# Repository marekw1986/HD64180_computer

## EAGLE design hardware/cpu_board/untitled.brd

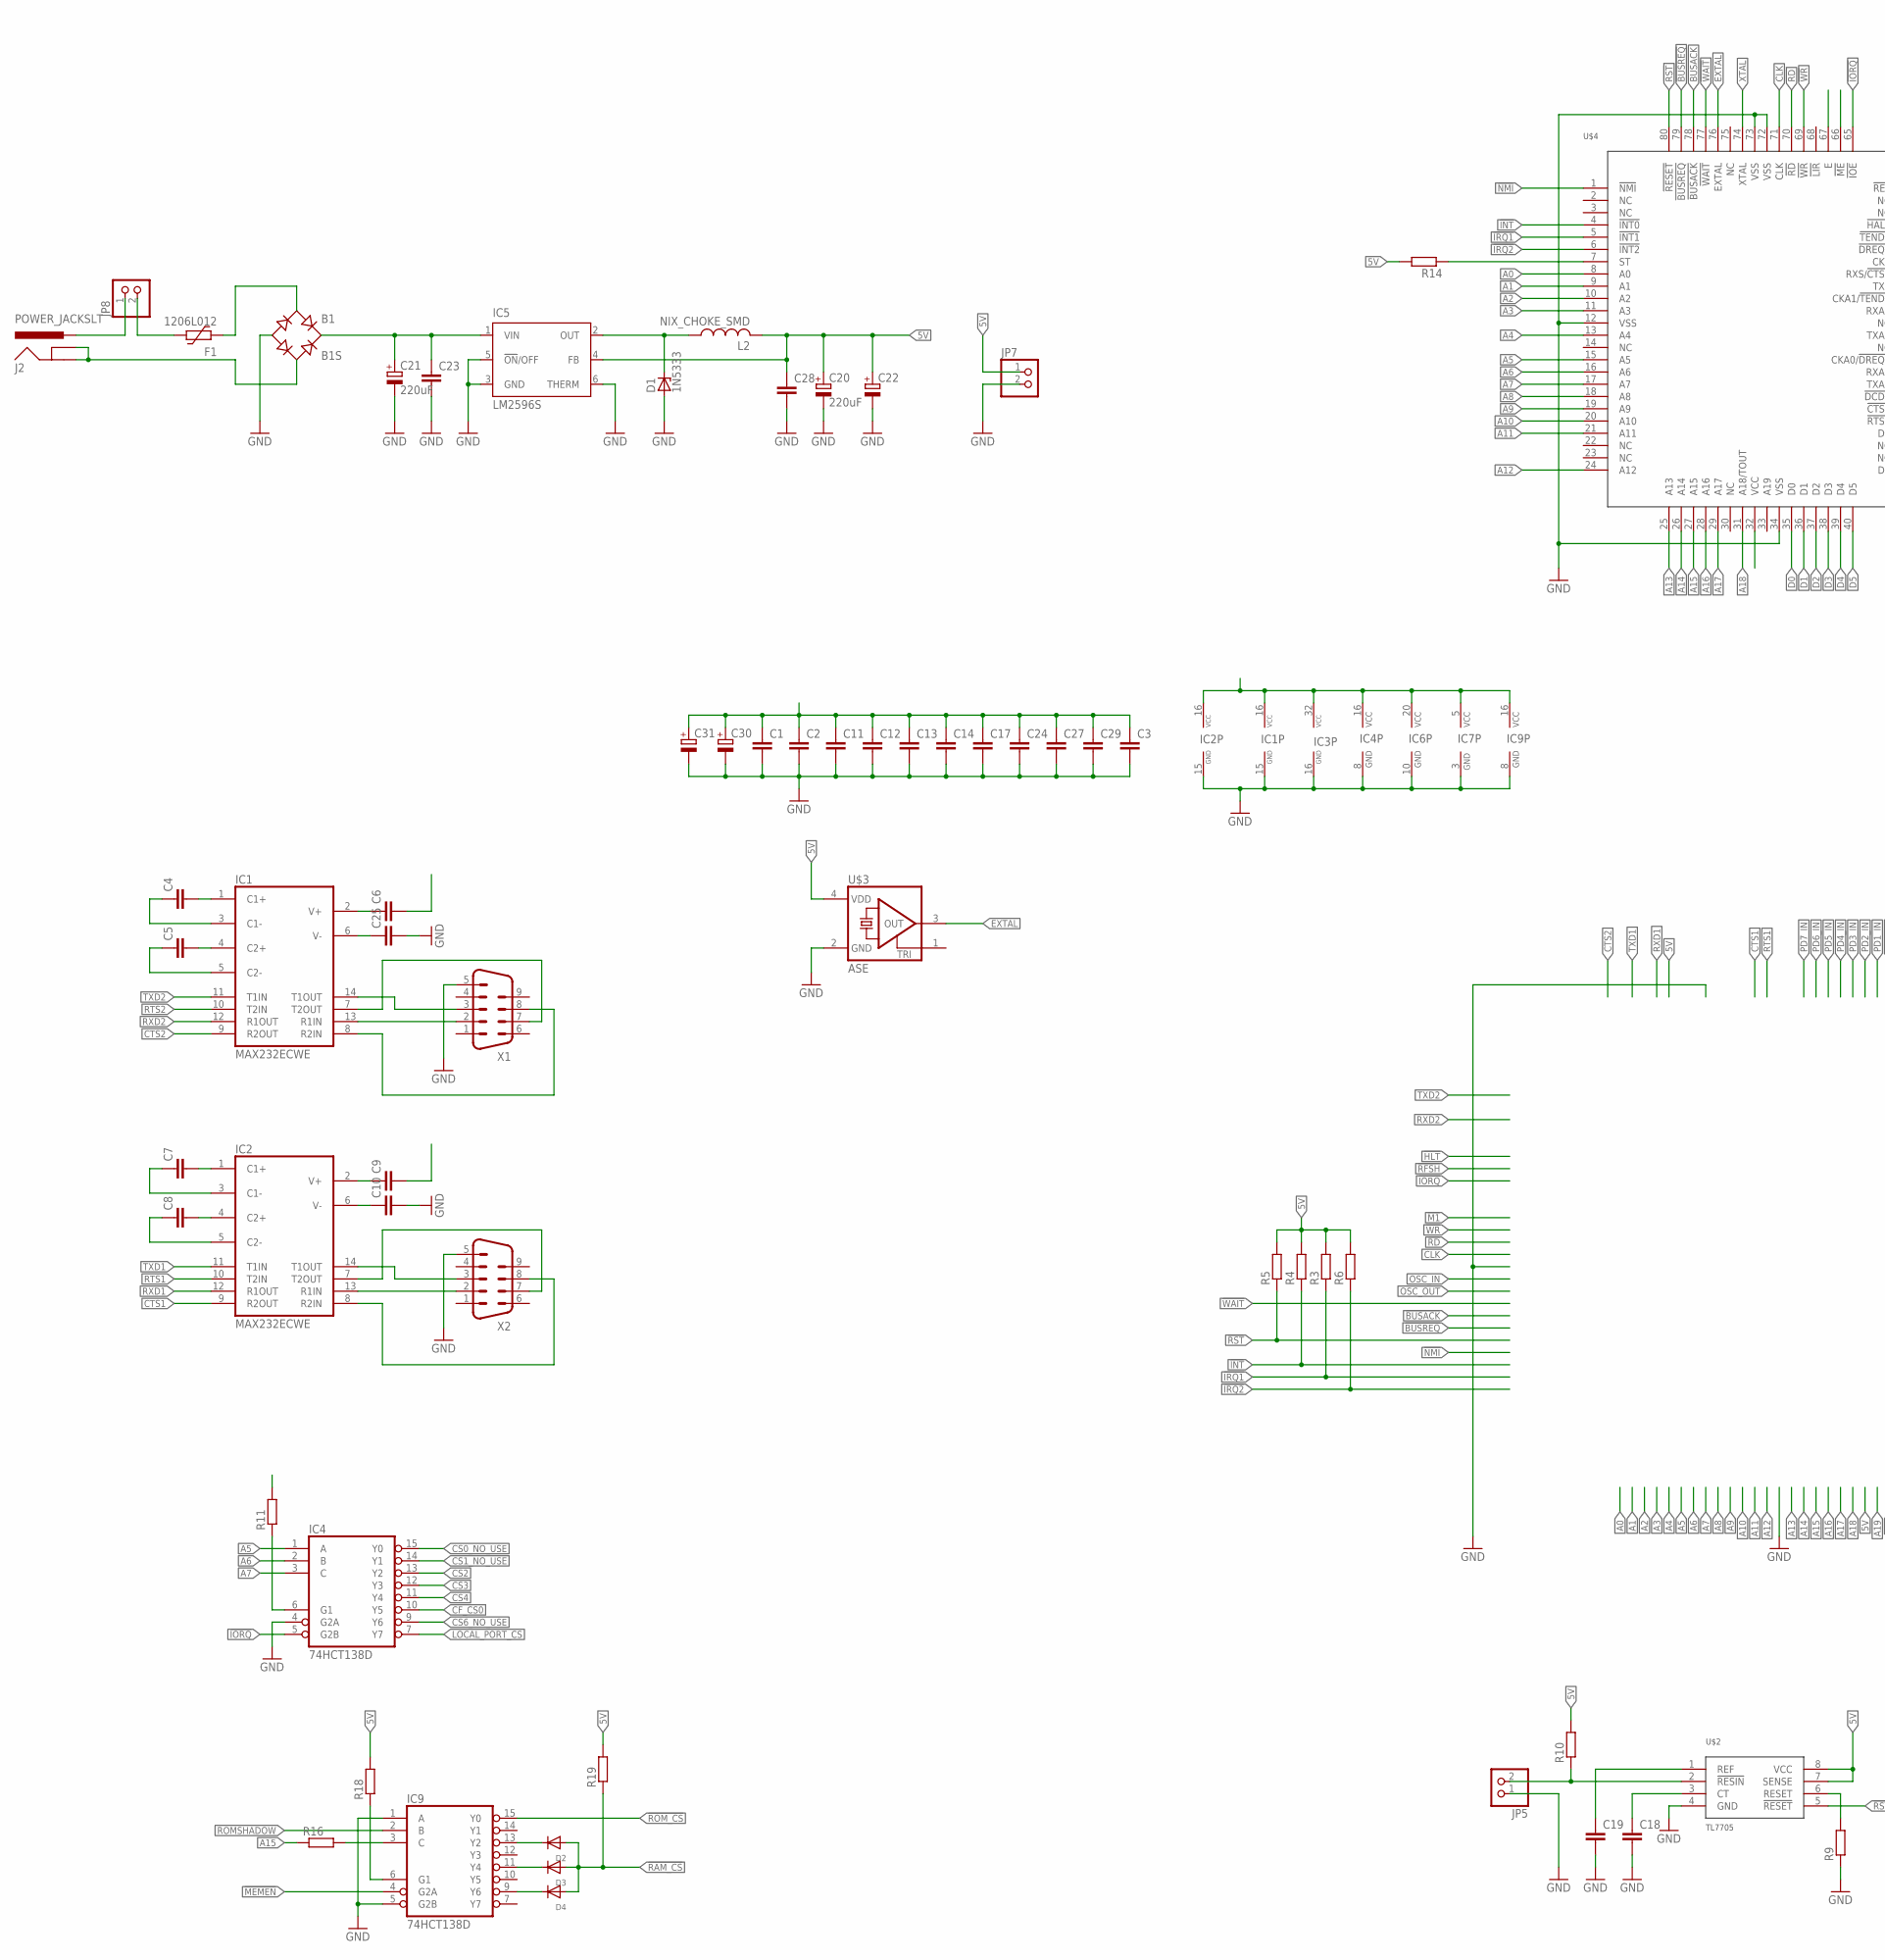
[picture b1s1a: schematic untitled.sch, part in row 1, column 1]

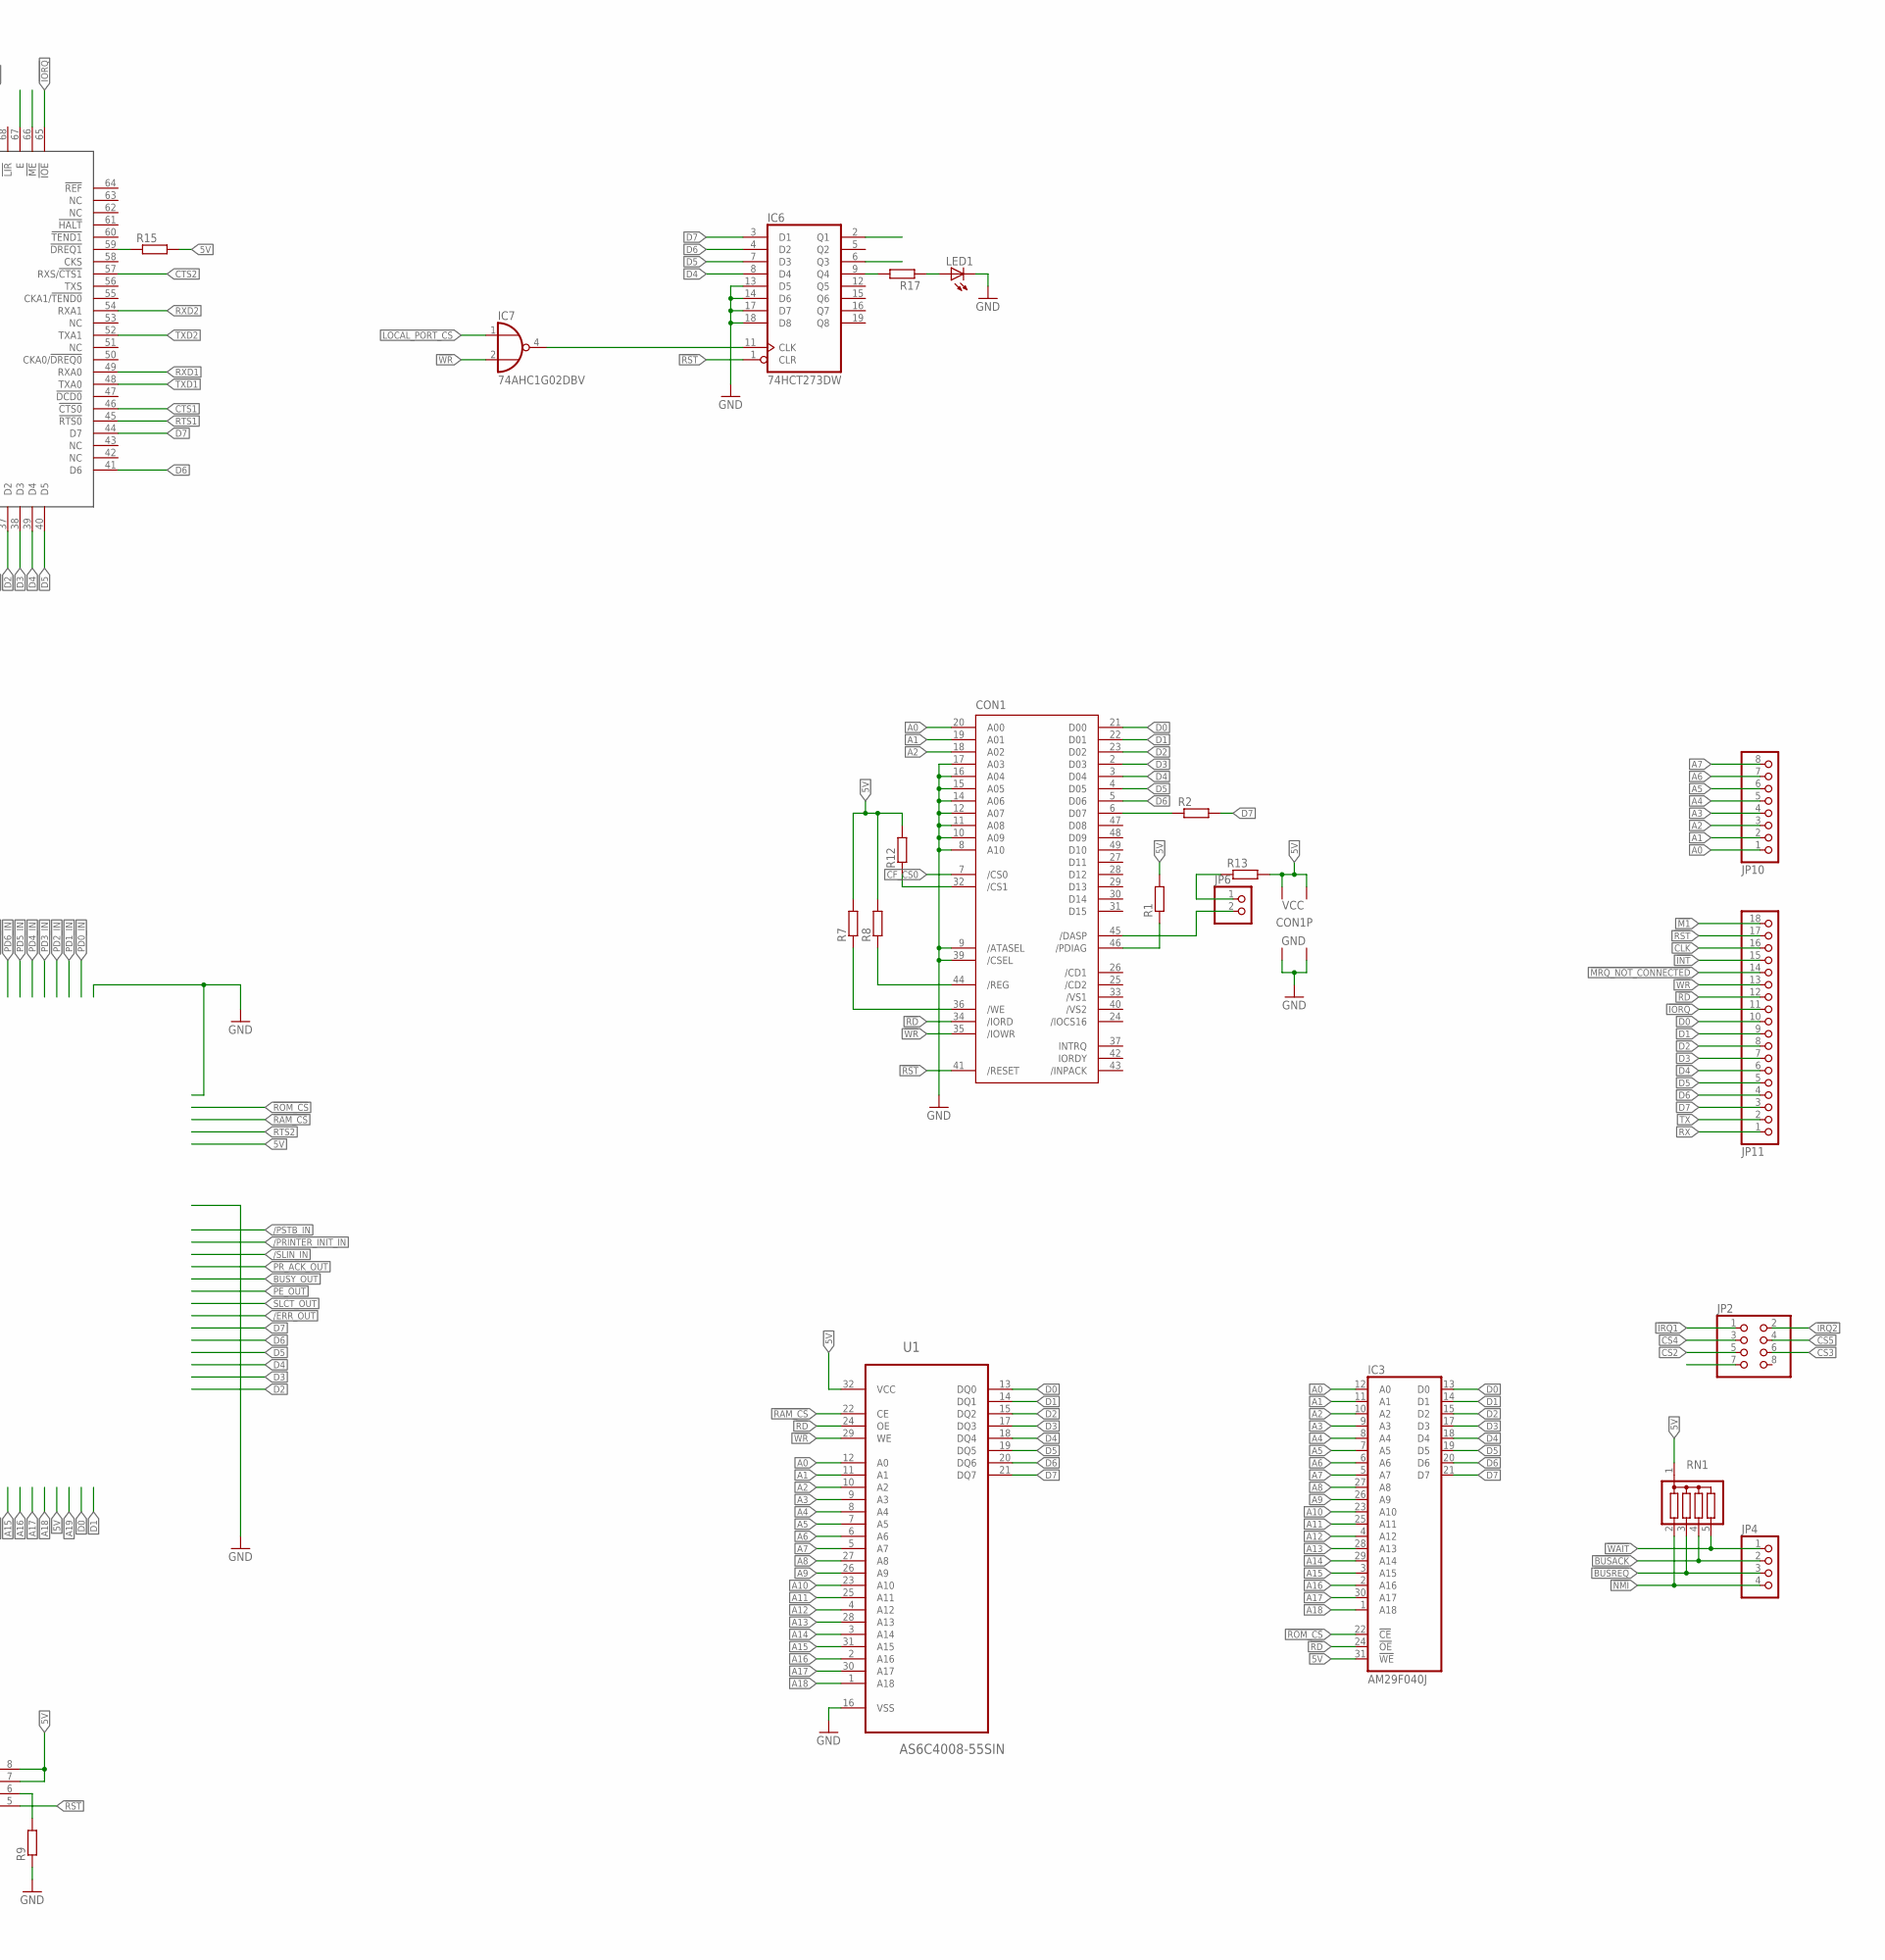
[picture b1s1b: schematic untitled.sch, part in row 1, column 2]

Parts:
B1: B1S; MBS
C1, C2, C3, C4, C5, C6, C7, C8, C9, C10, C11, C12, C14, C17, C18, C19, C23, C24, C25, C27, C28, C29: C-EUC0603; C0603
C13: C-EUC0402; C0402
C20, C21: 220uF; 153CLV-0810
C22: CPOL-EUSMCC; SMC_C
C30, C31: CPOL-EUSMCB; SMC_B
CON1: CF-CARD-IDE_MODE; MI20-50PD-SF
D1: 1N5333; C1702-15
D2, D3, D4: DIODESOD-323; SOD-323
F1: 1206L012; 1206L
IC1, IC2: MAX232ECWE; SO16L
IC3: AM29F040J; PLCC32R
IC4, IC9: 74HCT138D; SO16
IC5: LM2596S; TO263-5
IC6: 74HCT273DW; SO20W
IC7: 74AHC1G02DBV; SOT23-5
J2: POWER_JACKSLT; POWER_JACK_SLOT
JP2: PINHD-2X4; 2X04
JP4: PINHD-1X4; 1X04
JP5, JP6, JP7, JP8: PINHD-1X2; 1X02
JP10: PINHD-1X8; 1X08
JP11: PINHD-1X18; 1X18
L2: NIX_CHOKE_SMD
LED1: LEDCHIP-LED0603; CHIP-LED0603
R1, R2, R7, R8, R9, R11, R12, R13, R15, R16, R17, R18, R19: R-EU_R0603; R0603
R3, R4, R6: R-EU_R0402; R0402
R5: R-EU_R1206; R1206
R10: R-EU_M1206; M1206
R14: R-EU_0204/5; 0204/5
RN1: G04R; SIL5
U1: AS6C4008-55SIN; SOIC127P1407X299-32N
U$2: TL7705; SOIC8
U$3: ASE
U$4: HD64180QFP80_; QFP80
X1, X2: M09HP

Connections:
5V: C1.1, C2.1, C3.1, C6.2, C9.2, C11.1, C12.1, C13.1, C14.1, C17.1, C20.+, C22.+, C24.1, C27.1, C28.1, C29.1, C30.+, C31.+, CON1.13 (VCC2), CON1.38 (VCC1), IC1.16 (VCC), IC2.16 (VCC), IC3.31 (!WE), IC3.32 (VCC), IC4.16 (VCC), IC5.4 (FB), IC6.20 (VCC), IC7.5 (VCC), IC9.16 (VCC), JP7.1, L2.P$2 (2), R1.2, R3.2, R4.2, R5.2, R6.2, R7.2, R8.2, R10.2, R11.2, R12.2, R13.2, R14.2, R15.2, R18.2, R19.2, RN1.1, U1.32 (VCC), U$2.7 (SENSE), U$2.8 (VCC), U$3.4 (VDD), U$4.32 (VCC)
!BUSACK: JP4.2, RN1.4, U$4.78 (!BUSACK)
!BUSREQ: JP4.3, RN1.3, U$4.79 (!BUSREQ)
!INT: JP11.15, R4.1, U$4.4 (!INT0)
!IORQ: IC4.5 (G2B), JP11.11, U$4.65 (!IOE)
!IRQ1: JP2.1, R3.1, U$4.5 (!INT1)
!IRQ2: JP2.2, R6.1, U$4.6 (!INT2)
!M1: JP11.18
!MEMEN: IC9.4 (G2A), U$4.66 (!ME)
!MRQ_NOT_CONNECTED: JP11.14
!NMI: JP4.4, RN1.2, U$4.1 (!NMI)
!RAM_CS: D2.A, D3.A, D4.A, R19.1, U1.22 (CE)
!RD: CON1.34 (/IORD), IC3.24 (!OE), JP11.12, U1.24 (OE), U$4.70 (!RD)
!ROM_CS: IC3.22 (!CE), IC9.15 (Y0)
!RST: CON1.41 (/RESET), IC6.1 (CLR), JP11.17, R5.1, U$2.5 (!RESET), U$4.80 (!RESET)
!WAIT: JP4.1, RN1.5, U$4.77 (!WAIT)
!WR: CON1.35 (/IOWR), IC7.2 (I1), JP11.13, U1.29 (WE), U$4.69 (!WR)
A0: CON1.20 (A00), IC3.12 (A0), JP10.1, U1.12 (A0), U$4.8 (A0)
A1: CON1.19 (A01), IC3.11 (A1), JP10.2, U1.11 (A1), U$4.9 (A1)
A2: CON1.18 (A02), IC3.10 (A2), JP10.3, U1.10 (A2), U$4.10 (A2)
A3: IC3.9 (A3), JP10.4, U1.9 (A3), U$4.11 (A3)
A4: IC3.8 (A4), JP10.5, U1.8 (A4), U$4.13 (A4)
A5: IC3.7 (A5), IC4.1 (A), JP10.6, U1.7 (A5), U$4.15 (A5)
A6: IC3.6 (A6), IC4.2 (B), JP10.7, U1.6 (A6), U$4.16 (A6)
A7: IC3.5 (A7), IC4.3 (C), JP10.8, U1.5 (A7), U$4.17 (A7)
A8: IC3.27 (A8), U1.27 (A8), U$4.18 (A8)
A9: IC3.26 (A9), U1.26 (A9), U$4.19 (A9)
A10: IC3.23 (A10), U1.23 (A10), U$4.20 (A10)
A11: IC3.25 (A11), U1.25 (A11), U$4.21 (A11)
A12: IC3.4 (A12), U1.4 (A12), U$4.24 (A12)
A13: IC3.28 (A13), U1.28 (A13), U$4.25 (A13)
A14: IC3.29 (A14), U1.3 (A14), U$4.26 (A14)
A15: IC3.3 (A15), R16.1, U1.31 (A15), U$4.27 (A15)
A16: IC3.2 (A16), U1.2 (A16), U$4.28 (A16)
A17: IC3.30 (A17), U1.30 (A17), U$4.29 (A17)
A18: IC3.1 (A18), U1.1 (A18), U$4.31 (A18/TOUT)
CF_CS0: CON1.7 (/CS0), IC4.10 (Y5)
CLK: JP11.16, U$4.71 (CLK)
CS0_NO_USE: IC4.15 (Y0)
CS1_NO_USE: IC4.14 (Y1)
CS2: IC4.13 (Y2), JP2.5
CS3: IC4.12 (Y3), JP2.6
CS4: IC4.11 (Y4), JP2.3
CS5: JP2.4
CS6_NO_USE: IC4.9 (Y6)
CTS1: IC2.9 (R2OUT), U$4.46 (!CTS0)
CTS2: IC1.9 (R2OUT), U$4.57 (RXS/!CTS1)
D0: CON1.21 (D00), IC3.13 (D0), JP11.10, U1.13 (DQ0), U$4.35 (D0)
D1: CON1.22 (D01), IC3.14 (D1), JP11.9, U1.14 (DQ1), U$4.36 (D1)
D2: CON1.23 (D02), IC3.15 (D2), JP11.8, U1.15 (DQ2), U$4.37 (D2)
D3: CON1.2 (D03), IC3.17 (D3), JP11.7, U1.17 (DQ3), U$4.38 (D3)
D4: CON1.3 (D04), IC3.18 (D4), IC6.8 (D4), JP11.6, U1.18 (DQ4), U$4.39 (D4)
D5: CON1.4 (D05), IC3.19 (D5), IC6.7 (D3), JP11.5, U1.19 (DQ5), U$4.40 (D5)
D6: CON1.5 (D06), IC3.20 (D6), IC6.4 (D2), JP11.4, U1.20 (DQ6), U$4.41 (D6)
D7: IC3.21 (D7), IC6.3 (D1), JP11.3, R2.2, U1.21 (DQ7), U$4.44 (D7)
E: JP2.7, U$4.67 (E)
EXTAL: U$3.3 (OUT), U$4.76 (EXTAL)
GND: B1.-, C1.2, C2.2, C3.2, C10.2, C11.2, C12.2, C13.2, C14.2, C17.2, C18.2, C19.2, C20.-, C21.-, C22.-, C23.2, C24.2, C25.2, C27.2, C28.2, C29.2, C30.-, C31.-, CON1.1 (GND1), CON1.8 (A10), CON1.9 (/ATASEL), CON1.10 (A09), CON1.11 (A08), CON1.12 (A07), CON1.14 (A06), CON1.15 (A05), CON1.16 (A04), CON1.17 (A03), CON1.39 (/CSEL), CON1.50 (GND2), D1.A, IC1.15 (GND), IC2.15 (GND), IC3.16 (GND), IC4.4 (G2A), IC4.8 (GND), IC5.3 (GND), IC5.5 (!ON!/OFF), IC5.6 (THERM), IC6.10 (GND), IC6.13 (D5), IC6.14 (D6), IC6.17 (D7), IC6.18 (D8), IC7.3 (GND), IC9.1 (A), IC9.5 (G2B), IC9.8 (GND), JP5.1, JP7.2, LED1.C, R9.1, U1.16 (VSS), U$2.4 (GND), U$3.2 (GND), U$4.12 (VSS), U$4.34 (VSS), U$4.72 (VSS), U$4.73 (VSS), X1.5, X2.5
LOCAL_PORT_CS: IC4.7 (Y7), IC7.1 (I0)
unnamed: IC2.7 (T2OUT), X2.7
unnamed: C7.2, IC2.1 (C1+)
unnamed: C8.2, IC2.4 (C2+)
unnamed: C8.1, IC2.5 (C2-)
unnamed: C7.1, IC2.3 (C1-)
unnamed: C9.1, IC2.2 (V+)
unnamed: IC1.7 (T2OUT), X1.7
unnamed: IC1.13 (R1IN), X1.2
unnamed: C4.2, IC1.1 (C1+)
unnamed: C5.2, IC1.4 (C2+)
unnamed: C5.1, IC1.5 (C2-)
unnamed: C4.1, IC1.3 (C1-)
unnamed: C6.1, IC1.2 (V+)
unnamed: C25.1, IC1.6 (V-)
unnamed: IC2.13 (R1IN), X2.2
unnamed: IC2.14 (T1OUT), X2.3
unnamed: IC2.8 (R2IN), X2.8
unnamed: IC1.14 (T1OUT), X1.3
unnamed: C10.1, IC2.6 (V-)
unnamed: J2.PWR, JP8.1
unnamed: B1.AC1, F1.2
unnamed: B1.+, C21.+, C23.1, IC5.1 (VIN)
unnamed: D1.C, IC5.2 (OUT), L2.P$1 (1)
unnamed: B1.AC2, J2.GND@1 (GNDBREAK), J2.GND@2 (GND)
unnamed: R15.1, U$4.59 (!DREQ1)
unnamed: IC4.6 (G1), R11.1
unnamed: CON1.44 (/REG), R8.1
unnamed: IC1.8 (R2IN), X1.8
unnamed: CON1.36 (/WE), R7.1
unnamed: CON1.46 (/PDIAG), R1.1
unnamed: CON1.32 (/CS1), R12.1
unnamed: JP6.1, R13.1
unnamed: CON1.45 (/DASP), JP6.2
unnamed: CON1.6 (D07), R2.1
unnamed: R9.2, U$2.6 (RESET)
unnamed: C18.1, U$2.3 (CT)
unnamed: C19.1, U$2.1 (REF)
unnamed: JP5.2, R10.1, U$2.2 (!RESIN)
unnamed: F1.1, JP8.2
unnamed: IC6.11 (CLK), IC7.4 (O)
unnamed: IC6.9 (Q4), R17.2
unnamed: LED1.A, R17.1
unnamed: IC9.6 (G1), R18.1
unnamed: D2.C, IC9.13 (Y2)
unnamed: D4.C, IC9.9 (Y6)
unnamed: D3.C, IC9.11 (Y4)
ROMSHADOW: IC6.6 (Q3), IC9.2 (B)
RTS1: IC2.10 (T2IN), U$4.45 (!RTS0)
RTS2: IC1.10 (T2IN), IC6.2 (Q1)
RX: JP11.1
RXD1: IC2.12 (R1OUT), U$4.49 (RXA0)
RXD2: IC1.12 (R1OUT), U$4.54 (RXA1)
ST: R14.1, U$4.7 (ST)
TX: JP11.2
TXD1: IC2.11 (T1IN), U$4.48 (TXA0)
TXD2: IC1.11 (T1IN), U$4.52 (TXA1)
XTAL: U$4.74 (XTAL)
_A15: IC9.3 (C), R16.2

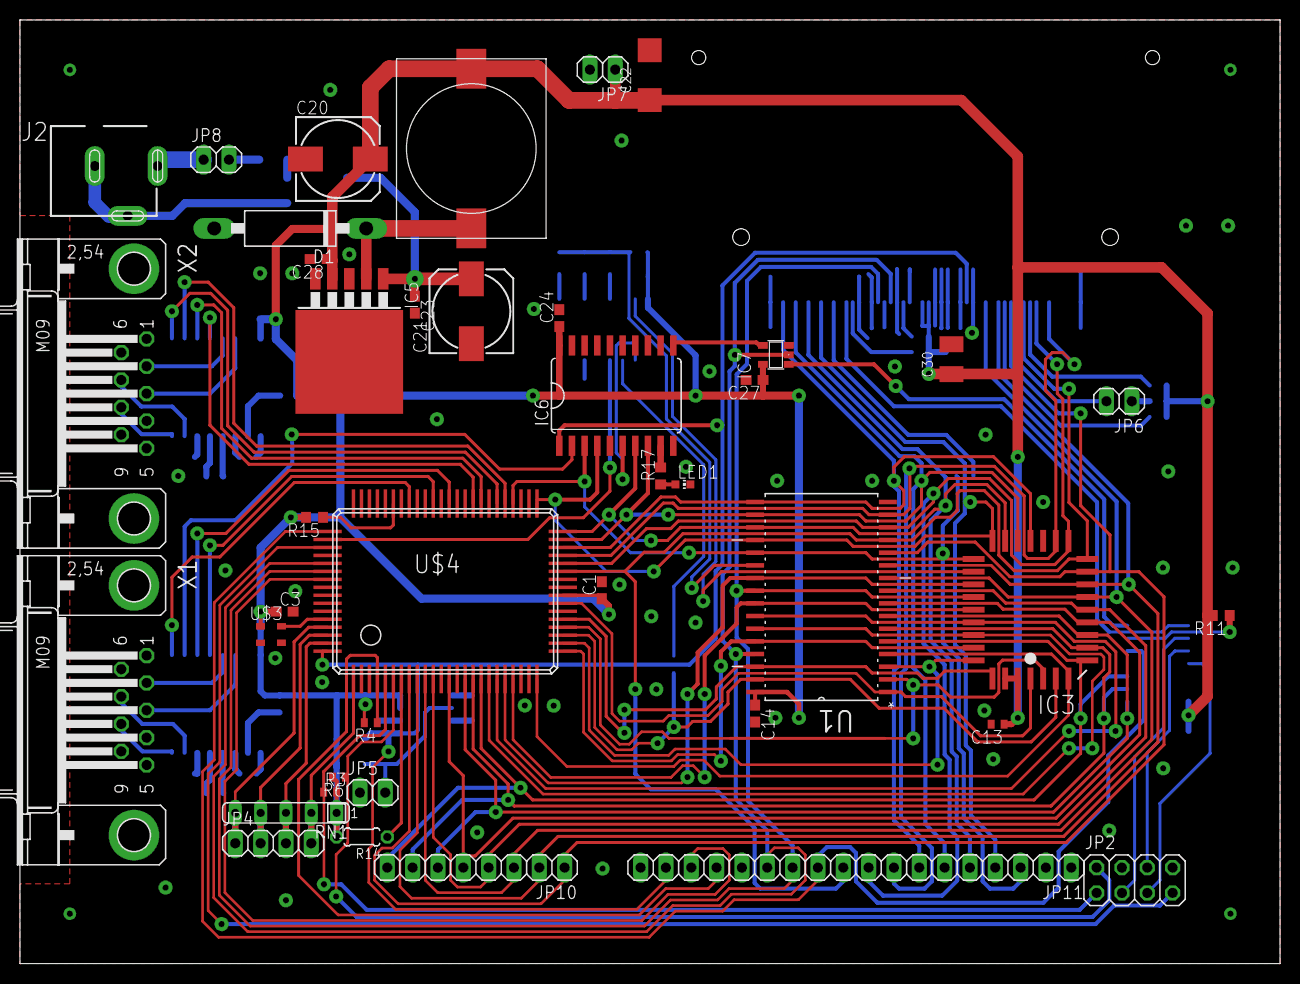
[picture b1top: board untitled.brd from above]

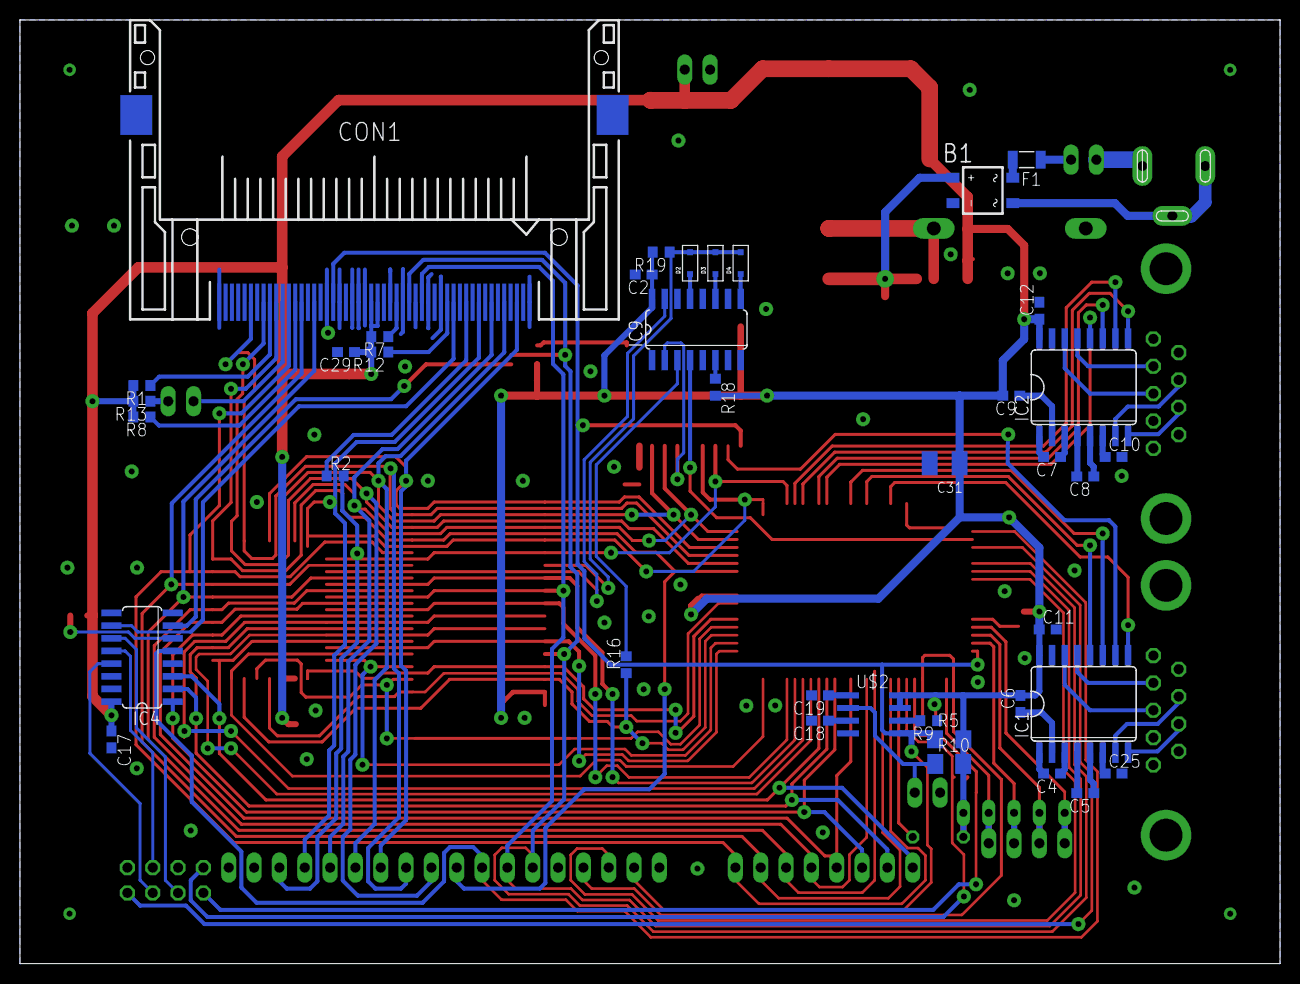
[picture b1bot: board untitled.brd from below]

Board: 2 copper layers, 126.3 x 94.6 mm, 80 parts (39 on the bottom side), 108 nets.

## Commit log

2025-10-06 PCB update
2025-10-07 PCB updated
2025-10-07 Minor update
2025-10-08 Data lines routed
2025-10-08 Another update
2025-10-08 Local port added
2025-10-08 E signal routed to edge connector
2025-10-08 Memory address decoder (work in progress)
2025-10-08 Minor changes
2025-10-08 Minor change
2025-10-08 VCC rerouted
2025-10-08 Writing to 273 fixed
2025-10-09 RAM/ROM address decoder (work in progress)
2025-10-09 ROM/RAM address decoder (version with diodes and wired-or on RAMCS line)
2025-10-09 Mionor bug fixed
2025-10-09 ROM/RAM address decoder bug fix
2025-10-09 Capacitor added
2025-10-10 Common files and definitions added
2025-10-10 Local port (SYSCFG) address added in definitions.asm
2025-10-12 Blink code added
2025-10-12 UART test added
2025-10-12 CP/M bootloader added
2025-10-12 CP/M added
2025-10-24 CPU size fixed
2025-11-10 Minor PCB update
2025-11-13 Cutout added to avoid accidental shoring of DB9 sockets shield to board ground
2026-01-10 PCB bug fix
2026-01-17 Bug fixes
2026-01-19 UART test code works now
2026-01-19 Bootloader update
2026-01-19 Changes in bootloader and CP/M bios
2026-01-19 Minor bug fix
2026-02-25 proper uart setting in uart_test
2026-02-25 Proper UART configuration for CP/M bootloader
2026-02-25 Bug fixed in CP/M BIOS uart driver

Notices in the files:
parts and their libraries:
SparkFun-Connectors: Licensing: Creative Commons ShareAlike 4.0 International - https://creativecommons.org/licenses/by-sa/4.0
